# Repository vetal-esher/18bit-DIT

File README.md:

# 18bit-DIT
Adding  digital output for old synths

Surely everyone who used to know DOS era met in games the choice of musical accompaniment - General MIDI, Roland Sound Canvas, Yamaha XG. I will not talk about what wonderful devices these are, and how well they played MIDI. Until the end of the 90s, all these home desktop romplers, like most other professional devices, had only analog outputs, however, they were quite acceptable in quality. In early 2010, out of nostalgia, I bought several devices of that era on ebay - these are the Roland Sound Canvas 88 Pro, <a href="https://github.com/vetal-esher/MT32-DIT">Roland MT-32</a>, Yamaha MU128 and Yamaha AN200. The first three should be familiar to gamers of the early 90s, while the AN200 module is an analog modeling synthesizer based on the Yamaha PLG150-AN plug-in card. Later Yamaha MU1000/2000 tone generators were also sold on the site - their difference from the MU128 consisted in a slightly expanded version of the sample bank, as well as in the presence of an optical TOSLINK output.

Actually, the presence of optics in the MU2000 prompted me to start comparing circuits to see if it was possible to modify the MU128 circuit and get a digital output on my own. In the MU2000 service manual, the optical output circuitry is based on a proprietary Yamaha YM3437C chip, which is very difficult to get for an ordinary radio amateur. We need to look for a more general DIT. A Google search on this topic led me to a <a href="https://nfggames.com/forum2/index.php?topic=4063.0">mod for MU10</a>. The author of the mod relied on the <a href="http://www3.big.or.jp/~fujikko/sc88vl/kaizo.html">Japanese mod for the Roland SC-88VL</a>. The mod is based on the TC9231N chip from Toshiba, which implements a digital audio interface according to the SPDIF/TOSLINK standard. The chip can be ordered on ebay, it costs an average of $ 2.5 per piece (note: this was in 2010, now the chip is almost impossible to find); the rest of the parts are sold at any radio store. I assembled a Japanese version on a breadboard, and it turned out to be working - with a small caveat. The DAC of the Roland SC88 is 18-bit, while the TC9231N is 16-bit. The Japanese author made a binding for this, which allows either cutting off the top 2 bits in the stream - which could lead to clipping, or shifting the stream 2 bits lower (cutting off the bottom 2 bits), which led to a decrease in volume. In any case, 2 bits of information were lost - and that did not suit me.

I started looking for a transceiver that works with 18-bit stream in "hardware" mode, i.e. that does not require setting the operating mode using an additional microcontroller. After a lot of experimentation with DIT 4096, 4192, TC9271N and others, I finally found a transceiver that works native with 18-bit stream - AKM AK4103AVF. Thanks to the internal pull-up and pull-down resistors, you can build the scheme by minimum of components.

Let's sketch out the diagram first. Given that the board should be as versatile as possible, all configurable pins should be placed on jumpers. The output is bound according to the datasheet as consumer S/PDIF. If XLR AES3 (AES/EBU) is needed, see AK4103 datasheet, also there you need another configuration on FS0-FS3 pins.

The input is I2S, for this we need the sdata, lrck(wclk), bck and mclk lines on the sources. In different datasheets, these lines may be called differently, but their essence is always the same - DATA=SDATA=SI=MDAC=SDTI, LRCK=LRCX=MWCLK, CLK=MQCLK=BCK, etc. All of these lines should be easily found in the circuits included in the DAC, with the exception of mclk, which will have to be searched by the oscilloscope at different points in the circuit. Usually, in I2S, mclk is not needed for transmission, but in AK4103AVF the line is used for correct synchronization.

It has been noticed that if the circuit is turned on at the same time as the module, the AK4103 does not pick up the frequency and the digital output is silent. Empirically revealed that the frequency is caught after the initialization of the module, you need a power delay. In 2016, without thinking twice, I simply brought the "spdif reset" button to the case (shown in the diagram). At the beginning of June 2022, <a href="https://github.com/nikitalita/MU100-DIT">nikitalita</a> contacted me and suggested to use the BRESET line in the PLG expansion connector. An oscilloscope check revealed that BRESET remained low for about 70ms, which was enough for the DIT to pick up the frequency. Let's find the lines on all three devices:

<table border=1>
<tr><th>I2S</th><th>Roland SC-88 Pro</th><th>Yamaha MU128</th><th>Yamaha AN200</th></tr>
<tr><td>mclk</td>	<td>CN105 pin 5</td>	<td>IC39 pin 16</td>	<td>IC17 pin 160</td></tr>
<tr><td>sdata</td>	<td>CN105 pin 3</td>	<td>IC36 pin 15</td>	<td>IC16 pin 15</td></tr>
<tr><td>bck</td>	<td>IC35 pin 8</td>	<td>IC36 pin 16</td>	<td>IC16 pin 16</td></tr>
<tr><td>wclk</td>	<td>CN105 pin 6</td>	<td>IC36 pin 13</td>	<td>IC16 pin 13</td></tr>
<tr><td>reset</td>	<td>IC35 pin 9</td>		<td>IC34 pin 19</td>	<td>CN5 pin 4</td></tr>
</table>

<h3>Roland SC-88 Pro</h3>

<h3>Yamaha MU128</h3>

<h3>Yamaha AN200</h3>

The SC88 has an 18-bit PCM69AU, while the MU128 and AN200 have an 18-bit NEC D63200. According to the specification, the SC-88 has a sample rate of 32kHz, MU128 and AN200 - 44kHz. Following the datasheet, we need to set the following modes: audio routing mode - normal, synchronous mode, 18bit right justified. Let's measure frequencies:
<table border=1>
<tr><th></th><th>wclk</th><th>mclk</th><th>bck</th><th>dif0</th><th>dif1</th><th>dif2</th><th>cks0</th><th>cks1</th><th>fs0</th><th>fs1</th><th>fs2</th><th>fs3</th></tr>

<tr><td>default</td><td>-</td><td>-</td><td>-</td><td>0</td><td>0</td><td>0</td><td>1</td><td>0</td><td>0</td><td>0</td><td>0</td><td>0</td></tr>
<tr><td>SC88</td>
<td>32000Hz</td><td>8.192 MHz</td><td>8.192 MHz</td>
<td>1</td><td>0</td><td>0</td>
<td>1</td><td>0</td>
<td>1</td><td>1</td><td>0</td><td>0</td>
</tr>
<tr><td>MU128</td>
<td>44100Hz</td><td>11.2896 MHz</td><td>2.8224 MHz</td>
<td>1</td><td>0</td><td>0</td>
<td>1</td><td>0</td>
<td>0</td><td>0</td><td>0</td><td>0</td>
</tr>
<tr><td>AN200</td>
<td>44100Hz</td><td>16.9344 MHz</td><td>2.8224 MHz</td>
<td>1</td><td>0</td><td>0</td>
<td>0</td><td>1</td>
<td>0</td><td>0</td><td>0</td><td>0</td>
</tr>
</table>

By the way, in 2010, the service manual for the MU128 could only be found on the same Ebay for money. I bought it, got a PDF, and immediately shared it on my site for free for everyone who seeks it. After a few weeks, this service manual was no longer sold :)

<p>This circuit was assembled on a breadboard and successfully worked in MU128 and AN200 in 2016.</p>

In 2021, I suddenly decided to re-release the development in a decent way.

<p>Gerbers: <a href="hardware/gerber/dit_0.2_gerber.zip">dit_0.2_gerber.zip</a></p>
<h2>Partlist</h2>
<table border=1>
<tr><th>Reference</th><th>Value</th><th>Package</th></tr>
<tr><td>U1</td><td>AK4103AVF</td><td>TSSOP-24</td></tr>
<tr><td>T1</td><td>PE-65612NL, TC-612</td><td></td></tr>
<tr><td>C1, C2, C3</td><td>100nF</td><td>0603</td></tr>
<tr><td>R1</td><td>330R</td><td>0402</td></tr>
<tr><td>R2</td><td>100R</td><td>0402</td></tr>
</table>

<h2>Roland SC88 Pro notes</h2>
<p>According to Japanese DIT project, the actual stream is 20bit, so AK4103 can be configured as 20-bit right justified, but you will get only significantly lower volume. This is the same melody recorded 20-bit first, then 18-bit:</p>

<h2>Links</h2>
<p><a href="https://esher.ru/blog/887.html">https://esher.ru/blog/887.html</a> My initial blog post in 2016 </p>
<p><a href="https://github.com/nikitalita/MU100-DIT">MU100-DIT</a>, a parallel project for MU-series using TOSLINK, by nikitalita</p>
<p><a href="https://kurohane.net/wiki/index.php?SC-88Pro%E3%81%AB%E5%85%89%E3%83%87%E3%82%B8%E3%82%BF%E3%83%AB%E5%87%BA%E5%8A%9B%E3%82%92%E4%BB%98%E3%81%91%E3%82%8B">Japanese project using AK4103 too</a></p>
<p><a href="https://esher.ru/i/f/887/887/AK4103AVF.pdf">AKM AK4103A datasheet</a></p>
<p><a href="https://esher.ru/i/f/900/900/an200sm.pdf.gz">Yamaha AN200 service manual</a></p>
<p><a href="https://esher.ru/i/f/888/888/Roland_SC-88Pro_ServiceNotes.pdf.gz">Roland SC88 Pro service notes (in japan)</a></p>
<p><a href="https://esher.ru/i/f/869/869/mu128sm-e.pdf.gz">Yamaha MU128 service manual</a></p>
<p><a href="https://github.com/vetal-esher/MT32-DIT">MT32-DIT, trying to SPDIF the legendary Roland MT-32</a></p>

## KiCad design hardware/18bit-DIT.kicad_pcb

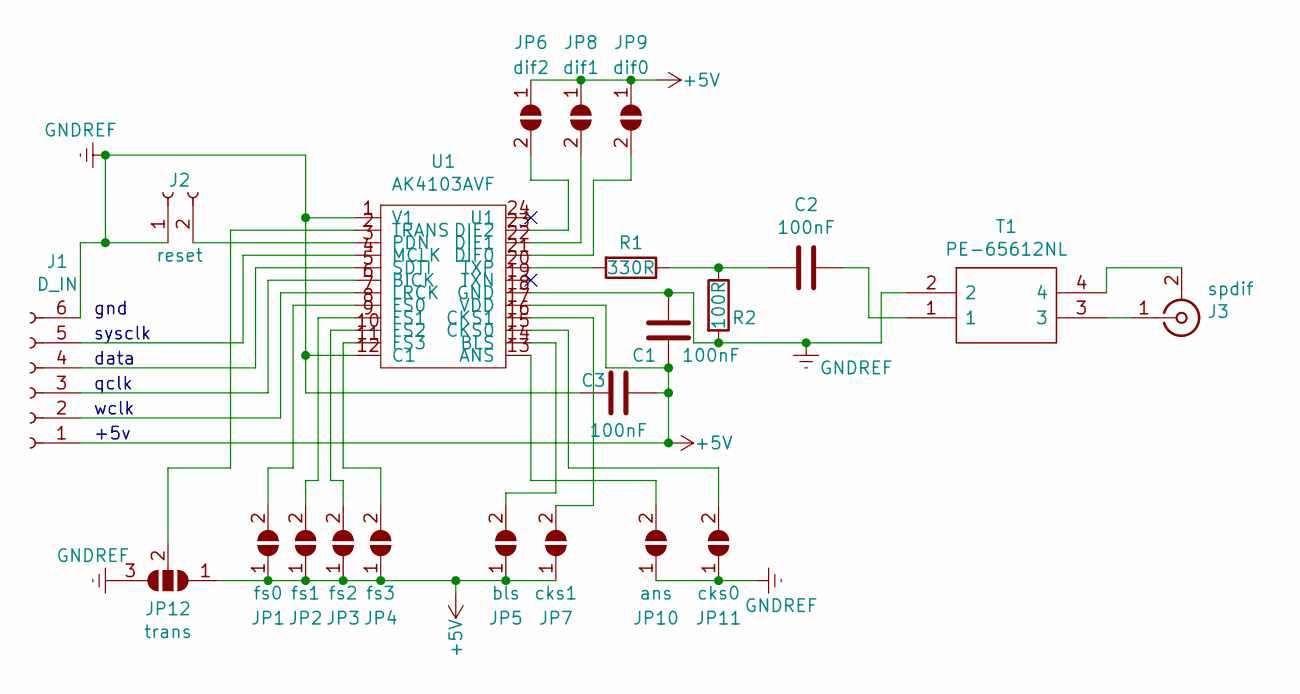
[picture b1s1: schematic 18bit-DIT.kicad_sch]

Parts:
C1, C2, C3: 100nF; C_0603_1608Metric
J1: D_IN; PinHeader_1x06_P2.54mm_Vertical
J2: reset; PinHeader_1x02_P2.54mm_Vertical
J3: spdif; TerminalBlock_bornier-2_P5.08mm
JP1: fs0; SolderJumper-2_P1.3mm_Open_RoundedPad1.0x1.5mm
JP2: fs1; SolderJumper-2_P1.3mm_Open_RoundedPad1.0x1.5mm
JP3: fs2; SolderJumper-2_P1.3mm_Open_RoundedPad1.0x1.5mm
JP4: fs3; SolderJumper-2_P1.3mm_Open_RoundedPad1.0x1.5mm
JP5: bls; SolderJumper-2_P1.3mm_Open_RoundedPad1.0x1.5mm
JP6: dif2; SolderJumper-2_P1.3mm_Open_RoundedPad1.0x1.5mm
JP7: cks1; SolderJumper-2_P1.3mm_Open_RoundedPad1.0x1.5mm
JP8: dif1; SolderJumper-2_P1.3mm_Open_RoundedPad1.0x1.5mm
JP9: dif0; SolderJumper-2_P1.3mm_Open_RoundedPad1.0x1.5mm
JP10: ans; SolderJumper-2_P1.3mm_Open_RoundedPad1.0x1.5mm
JP11: cks0; SolderJumper-2_P1.3mm_Open_RoundedPad1.0x1.5mm
JP12: trans; SolderJumper-3_P1.3mm_Open_RoundedPad1.0x1.5mm_NumberLabels
R1: 330R; R_0402_1005Metric
R2: 100R; R_0402_1005Metric
T1: PE-65612NL; PE65612NL; Manufacturer_Part_Number PE-65612NL; Mouser Part Number 673-PE-65612NL
U1: AK4103AVF; TSSOP-24_6.1x7.8mm_P0.65mm

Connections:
+5V: C1.2, C3.1, J1.1, JP1.1 (A), JP2.1 (A), JP3.1 (A), JP4.1 (A), JP5.1 (A), JP6.1 (A), JP7.1 (A), JP8.1 (A), JP9.1 (A), JP12.1 (A), U1.17 (VDD)
GNDREF: C1.1, C3.2, J1.6, J2.1, JP10.1 (A), JP11.1 (A), JP12.3 (B), R2.2, T1.2, U1.1 (V1), U1.12 (C1), U1.18 (GND)
unnamed: C2.1, T1.1
unnamed: C2.2, R1.1, R2.1
unnamed: J1.2, U1.7 (LRCK)
unnamed: J1.3, U1.6 (BICK)
unnamed: J1.4, U1.5 (SDTI)
unnamed: J1.5, U1.4 (MCLK)
unnamed: J2.2, U1.3 (PDN)
unnamed: J3.1 (In), T1.3
unnamed: J3.2 (Ext), T1.4
unnamed: JP1.2 (B), U1.8 (FS0)
unnamed: JP2.2 (B), U1.9 (FS1)
unnamed: JP3.2 (B), U1.10 (FS2)
unnamed: JP4.2 (B), U1.11 (FS3)
unnamed: JP5.2 (B), U1.14 (BLS)
unnamed: JP7.2 (B), U1.16 (CKS1)
unnamed: JP10.2 (B), U1.13 (ANS)
unnamed: JP11.2 (B), U1.15 (CKS0)
unnamed: JP12.2 (C), U1.2 (TRANS)
unnamed: R1.2, U1.20 (TXP)
unnamed: JP9.2 (B), U1.21 (DIF0)
unnamed: JP8.2 (B), U1.22 (DIF1)
unnamed: JP6.2 (B), U1.23 (DIF2)

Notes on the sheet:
+5v
sysclk
qclk
gnd
data
wclk

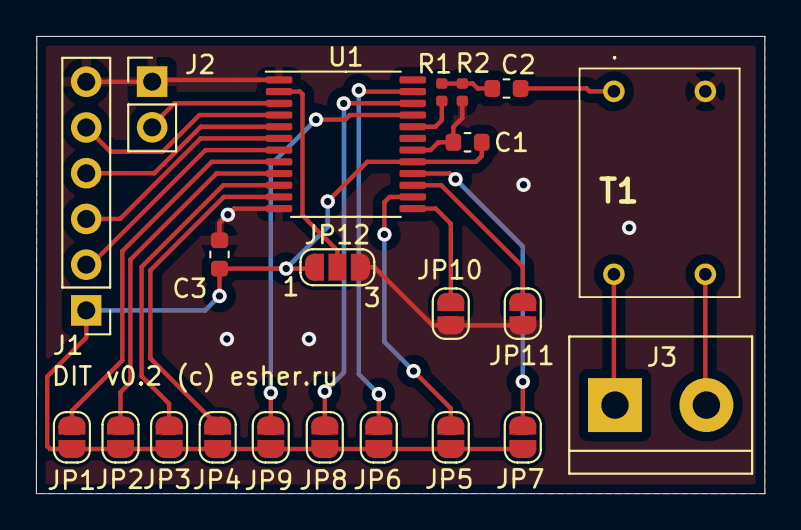
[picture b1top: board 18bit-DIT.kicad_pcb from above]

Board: 2 copper layers, 40.5 x 25.4 mm, 22 parts (0 on the bottom side), 24 nets.

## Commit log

2022-07-04 links added
2023-03-13 update clk names
